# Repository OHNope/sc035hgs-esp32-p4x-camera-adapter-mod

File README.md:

# SC035HGS Camera Adapter Mod

[中文](#中文) | [English](#english)

---

## 中文

本仓库在 [ESP32-P4X_MIPI_Camera_Sub_V1.1_KiCAD](https://github.com/OHNope/ESP32-P4X_MIPI_Camera_Sub_V1.1_KiCAD)（Espressif 官方相机转接板的 KiCad 转换版）基础上，修改为 SC035HGS 相机模组用的转接板。基础工程（导入修复、检查结果）的说明见它的 [README](https://github.com/OHNope/ESP32-P4X_MIPI_Camera_Sub_V1.1_KiCAD#readme)。

### 原理图改动

依据：SC035HGS 数据手册 V0.8、模组图纸（24P FPC，0.5 mm 间距，0.3 mm 厚，触点在模组背面）、[ESP32-P4-Function-EV-Board v1.5.2 原理图](sources/esp32-p4-function-ev-board-schematics_v1.52.pdf)。模组图纸上标的传感器是 SC035GS；SC035HGS 是它的升级版，完全兼容，FPC 引脚定义不变。

**J2（模组 FPC）**：沿用原连接器 FPC-05F-24PH20（24P，0.5 mm，翻盖下接）和封装 `Camera_Sub:FFC_24P_0P5`。FPC 触点朝下插入时，模组第 n 脚落在焊盘 n 上，所以封装几何不变，只重做引脚定义。新符号 `SC035HGS_Mod:SC035HGS_FPC_24P` 的引脚名与模组图纸一致：

| J2 | 模组 | 网络 | J2 | 模组 | 网络 |
|----|------|------|----|------|------|
| 1 | LED-strobe | `/LED_STROBE` | 13–16 | NC | — |
| 2 | TRIG | `/TRIG` | 17, 20 | GND | GND |
| 3 | PWDN (xshutdn) | `/XSHUTDN` | 18 / 19 | MIPI_RCN / RCP | `/CSI_CLKN` / `/CSI_CLKP` |
| 4 | NC | — | 21 | MCLK | `/MCLK` |
| 5 / 6 | SDA / SCL | `/SENSOR_SDA` / `/SENSOR_SCL` | 22 | DOVDD 1.8 V | DOVDD_1V8 |
| 7, 8 | GND | GND | 23 | DVDD 1.5 V | DVDD_1V5 |
| 9 / 10 | MIPI_RDN0 / RDP0 | `/CSI_DATA0N` / `P` | 24 | AVDD 2.8 V | AVDD_2V8 |
| 11 / 12 | MIPI_RDN1 / RDP1 | `/CSI_DATA1N` / `P` | 25, 26 | 固定焊盘 | GND |

**电源**：新增 U3 ME6211C15M5G-N（LCSC C53100）提供 DVDD 1.5 V。上电顺序按手册 DOVDD → DVDD → AVDD：U1 EN 接 3V3，U3 EN 经 R12/C18 接 DOVDD_1V8，U2 EN 经 R14/C15 接 DVDD_1V5，各有约 1 ms 的 RC 延时，前一路稳定后下一路才开启。

**控制信号**：传感器侧都是 1.8 V（输入上限 DOVDD+0.3 V），主板和 J3 都是 3.3 V。三路都用 SN74LVC1G07 开漏缓冲（VCC=1.8 V，输入/输出可耐 5.5 V）做电平转换：

- XSHUTDN（U4）：输入 `/XSHUTDN_3V3` 来自 J1.5 和 J3.3，R24 上拉，默认使能。输出经 R10/C3 延时，XSHUTDN 在 DOVDD 上电或 J3.3 释放后约 12–14 ms 才达到高电平（手册只要求 AVDD 稳定后再拉高，T3 ≥ 0）。SW1 和 J3.3 拉低 XSHUTDN 是让传感器进入休眠，寄存器内容保留，并不是复位（手册 p.14）。原来 J1.5 直接接到 1.8 V 复位网络，主板 3.3 V 上拉和板上 1.8 V 上拉分压后约 2.55 V，超过 SC035HGS 的绝对最大值，所以改为缓冲。
- TRIG（U5）：J3.1 → TRIG，R26 2.2 kΩ 上拉，R25 让 J3 悬空时保持低电平。外触发模式下上升沿开始曝光。
- LED_STROBE（U6）：J2.1 → J3.2，R28 上拉到 3V3，R27 让传感器关断时输出保持低电平。

**J3**：JAE IL-G-4P-S3L2-SA（2.5 mm 间距，卧式，摩擦锁），线端配 IL-G-4S-S3C2-SA。1 TRIG_3V3、2 LED_STROBE_3V3、3 XSHUTDN_3V3、4 GND，接到 P4 开发板的 GPIO 排针。封装 `SC035HGS_Mod:JAE_IL-G-4P-S3L2-SA_1x04_P2.50mm_Horizontal` 按 JAE 图纸 SJ019575 画：1 脚编号与 JAE 一致（元件面看，开口朝 +Y 时 1 脚在左），孔径 1.1 mm，焊盘沿用社团的椭圆焊盘；板边应距针排 7–8.5 mm。注意：社团原有 IL-G 封装的 1 脚编号与 JAE 相反，用社团线束时要按 JAE 编号核对。EV 板 CSI 座的 CAM_IO0/CAM_IO1（对应 J1.5/J1.4）没有接到任何 GPIO，CAM_IO0 只有上拉（EV-Board 原理图 p.3：J9.11 CAM_IO0 只接 R123 10 kΩ 到 3.3 V，J9.12 CAM_IO1 的 R111 不贴），所以必须通过 J3 控制。J1.4 保持不接。

**C12/C13/C14**：值标为 NC 的三颗电容在原理图和 PCB 上都设为 DNP（不贴）。

**网络改名**：`RESET` → `XSHUTDN`（1.8 V）/ `XSHUTDN_3V3`（3.3 V），`XVCLK` → `MCLK`。新增器件放在项目库 `libraries/SC035HGS_Mod.*`（符号和封装），连接器出线方向等元数据在 `libraries/manifest.json`；`orcad_import` / `Camera_Sub` 与上游保持一致。

**固件注意**：
- 首次 I2C 访问：XSHUTDN 变高且 MCLK 已在运行后至少等 4 ms（手册 p.13 图 1-4 的 T4）。板上 XSHUTDN 由 R10/C3 延时，所以上电或释放 J3.3 后至少等约 20 ms 再访问传感器。
- 需要恢复默认寄存器时写 `0x0103=0x01`（软复位），拉低 XSHUTDN 不会清除寄存器。
- MCLK 为 24 MHz。写 `0x0100=0x01` 后至少等 7 ms，再写 `0x4418`/`0x4419`（SmartSens 配置说明）。
- 外触发模式：`0x3222[1]=1`。STROBE 使能：`0x3361[7:6]=00`。
- I2C 地址由模组内部的 SID0/SID1 决定（FPC 未引出），首次上电请扫描 0x30–0x33 确认。

### PCB

PCB 在 KiCad 里按新原理图更新后全部重做：旧铜皮全部删除，重新摆放和走线。

- **板框与叠层**：40 × 24 mm，R3 圆角。4 层，嘉立创 JLC04161H-7628 叠层，1.6 mm，沉金（ENIG）；加工参数在 [`pcb-fabrication-profile.json`](pcb-fabrication-profile.json)，Board Setup 的工艺下限也按它设置。
- **布局**：J1（接 P4 开发板的 FPC）在下边，J2（模组 FPC）在上边，J3 在右边、开口朝板外，SW1 在右上角。
- **层分配**：In1 整层 GND，In2 整层 DOVDD_1V8；顶层和底层走信号并铺 GND。3V3、DVDD_1V5、AVDD_2V8 走线，线宽按 SC035HGS 最大 120 mW 的电流算，对应网络类 `PWR_*`。
- **MIPI CSI-2**：三对差分全部走顶层、不打孔，100 Ω（线宽 0.2258 mm，间距 0.2032 mm），以 In1 为参考面；每次转弯只用一个 45° 折角，对内长度差为 0，三对之间的长度差 0.21 mm。
- **过孔**：全部 0.6/0.3 mm。
- **丝印**：字高 1.0 mm、线宽 0.15 mm（嘉立创下限）；放不下的位号移到 Fab 层。底面丝印为板名和 "Same-Side FFC" 提示。
- **清理**：删除了 Allegro 导入时留下的尺寸标注（MECH1/MECH2）、钻孔表、板外的空规则区和右边缘的旧 Route Keepin 规则区；底面丝印上 Espressif 的 logo 和 WEEE/ESD/无铅/无卤标志也已删除。
- **位置**：板子放在 A4 图框正中（板框 x 128.5–168.5 mm，y 93–117 mm），出图时板子在图框内。
- **检查**：ERC 0；DRC 0 错误、0 未连接，与原理图一致。剩余 87 条警告都是丝印：57 条是相邻 `Camera_Sub` 库封装的丝印互相碰到（封装丝印超出 courtyard），30 条是丝印压在焊盘上（主要是 J1/SW1，生产时由阻焊裁掉），不影响加工。

`sources/espressif-original/` 里是 Espressif 原板的 BOM、贴片坐标和 PCB 加工说明，对应的是旧版 32 mm 板，**不能用来给本板下单**。本板的 Gerber、BOM 和贴片文件由 `-fab` 发布生成，下单用最新的 `v0.9.1-fab`。

### 上电调试

首批板子上电时逐项确认，结果补记在这里：

- [ ] **MCLK 占空比**：Y1 没有可查的数据手册。在 J2.21 测 24 MHz 波形，占空比应在 45–55 %，高、低电平各至少 5 ns（SC035HGS 手册 p.37）。
- [ ] **各路电流**：手册 V0.8 p.36 的工作电流是空白的，分别测 DOVDD_1V8、DVDD_1V5、AVDD_2V8 的电流。按手册 p.2 的最大功耗 120 mW 推算，单路上限约为 DOVDD 67 mA、DVDD 80 mA、AVDD 43 mA，都在 ME6211 的额定范围内；测得值明显更大时先断电排查。
- [ ] **I2C 地址**：在 0x30–0x33 范围扫描，记下模组的实际地址。
- [ ] **J3 → P4 GPIO**：J3 接 EV 板的 GPIO 排针（J1，2×20）时，避开启动 strapping 引脚 GPIO34–GPIO38；排针上是 GPIO37（8 脚）、GPIO38（10 脚）和 GPIO36（24 脚）（EV-Board 原理图 p.3）。P4 复位期间本板会给 J3 加上固定电平：J3.3 经 R24 上拉到 3V3，J3.1 经 R25 下拉，DOVDD 有电且 STROBE 空闲时 J3.2 被 U6 拉低，接在 strapping 引脚上可能改变启动模式。J3.1（TRIG）和 J3.3（XSHUTDN）的 GPIO 设为推挽输出（U4/U5 的输入要求快边沿），J3.2（STROBE）设为输入，J3.4 接排针上的 GND。选定的 GPIO 记在这里。
- [ ] **J3 实物配合（可选）**：封装已按 JAE 图纸 SJ019575 核对；有 IL-G-4P-S3L2-SA 样品时，可再实际插装确认孔位和板边距离。

**已接受的风险**（2026-10-03 决定本版不改）：

- **突然断电时的 XSHUTDN**：手册图 1-5 要求断电前先拉低 XSHUTDN。3V3 突然断开时，C3（R10 × C3 = 10 ms）会让 XSHUTDN 在 DOVDD 已经下降后仍短暂保持高电平，可能超过 DOVDD + 0.3 V 的绝对最大值。能量很小，Espressif 原板的 RESET RC 也是如此。正常关机时先把 J3.3 拉低再断电即可避免。若要修改：在 R10 两端并联一个二极管（阳极接 /XSHUTDN，阴极接 DOVDD_1V8）。
- **U4 直接给 C3 放电**：U4 拉低 XSHUTDN 时，C3（1 µF）经 U4 输出直接放电，中间没有电阻。峰值灌电流只受 U4 输出电阻限制，超过推荐的 4 mA IOL，在几十微秒内可能接近 50 mA 的绝对最大值。若要修改：在 U4.4 与 R10/C3/J2.3 节点之间串 100–220 Ω。

**下一版待改**：U4 的 Description 字段写的是 "R10 + C3 set the >=4 ms power-up delay"，这个说法不对。手册的 4 ms（T4，p.13）是 XSHUTDN 变高到第一次 I2C 访问之间的时间，由固件等待（见上文“固件注意”）；R10/C3 的作用是让 XSHUTDN 在 AVDD 之后变高（T3 ≥ 0）。下一版改为 "R10 + C3 delay XSHUTDN high ~12 ms after DOVDD (T3 >= 0); firmware waits >= 4 ms (T4) before I2C"。这只是字段文字，不影响网表和 PCB，本版不改。

### 仓库关系

| Remote     | 仓库                                         | 用途                        |
|------------|----------------------------------------------|-----------------------------|
| `origin`   | `OHNope/sc035hgs-esp32-p4x-camera-adapter-mod` | 本仓库，改版开发            |
| `upstream` | `OHNope/ESP32-P4X_MIPI_Camera_Sub_V1.1_KiCAD`  | 基础工程，只拉取，不推送    |

基础工程有更新时合并进来：

```bash
git fetch upstream
git merge upstream/main
```

工程文件名 `SCH_ESP32-P4_FUNCTION_EV_BOARD_MIPI_Camera_Sub_V1.1_20240529.*` 与基础工程保持一致，不要改名，否则上游修改无法直接合并。本仓库的 README.md 是改版说明，合并时 README.md 有冲突就保留本仓库的版本（`git checkout --ours README.md`）。

### 发布

[`.github/workflows/pcb-release.yml`](.github/workflows/pcb-release.yml) 调用共享流水线 [OHNope/kicad-release](https://github.com/OHNope/kicad-release)，标签规则、各次发布的内容和 Google Drive 配置都以那边的 README 为准。

| 标签 | 内容 |
|------|------|
| `v0.9.0` | 只有 SC035HGS 原理图，PCB 还是旧板 |
| `v0.9.1-fab` | 第一版 PCB 的加工文件（Gerber、钻孔、BOM、贴片坐标），用于打样；贴片坐标不含不贴的 C12–C14。没有单独的 `v0.9.1` 设计发布 |

```bash
git tag -a v0.9.1 -m "v0.9.1: ..." && git push origin v0.9.1
```

```bash
git tag -a v0.9.1-fab -m "v0.9.1-fab: ..." "v0.9.1^{}" && git push origin v0.9.1-fab
```

`v0.9.1` 发布原理图/PCB 文档，并把已提交的整个工程目录传到 Drive；`v0.9.1-fab` 才发布 Gerber，且必须与 `v0.9.1` 指向同一个 commit，所以先推设计标签、再推 `-fab`。C12–C14 在 F.Paste 上仍有钢网开口，下单 SMT 时以 BOM 和贴片坐标为准。Google Drive 需要在 Settings → Secrets and variables → Actions 中设置 secret `GDRIVE_TOKEN` 和 variable `GDRIVE_FOLDER_ID`。

### kicad-auto

`.kicad-auto/` 是 kicad-auto 工具的本地状态（评审、语义分析、生成工作区），已加入 `.gitignore`，不提交。

### 版权与许可

设计版权归 Espressif Systems (Shanghai) Co., Ltd. 所有。本仓库**不授予任何许可**，详见 [LICENSE](LICENSE)。本仓库为非营利性的学习与参考分享，与 Espressif 无关联、未获其背书；如 Espressif 提出异议，将立即删除。

---

## English

This repository modifies [ESP32-P4X_MIPI_Camera_Sub_V1.1_KiCAD](https://github.com/OHNope/ESP32-P4X_MIPI_Camera_Sub_V1.1_KiCAD), the KiCad conversion of Espressif's camera adapter board, into an adapter for the SC035HGS camera module. See its [README](https://github.com/OHNope/ESP32-P4X_MIPI_Camera_Sub_V1.1_KiCAD#readme) for the base project (import fixes, check results).

### Schematic changes

Sources: SC035HGS datasheet V0.8, the module drawing (24-pin FPC, 0.5 mm pitch, 0.3 mm thick, contacts on the module's bottom side), [ESP32-P4-Function-EV-Board v1.5.2 schematic](sources/esp32-p4-function-ev-board-schematics_v1.52.pdf). The module drawing names the sensor SC035GS; SC035HGS is its fully compatible upgrade, so the FPC pinout is unchanged.

- **J2 (module FPC)**: same connector (FPC-05F-24PH20, 24-pin 0.5 mm flip-lock, bottom contact) and footprint `Camera_Sub:FFC_24P_0P5`. With the FPC inserted contacts-down, module pin n lands on pad n, so only the pin assignment changes. The new symbol `SC035HGS_Mod:SC035HGS_FPC_24P` uses the module's pin names; see the table in the Chinese section.
- **Power**: U3 ME6211C15M5G-N (LCSC C53100) adds DVDD 1.5 V. Power-up order follows the datasheet (DOVDD → DVDD → AVDD): U1 EN from 3V3, U3 EN from DOVDD_1V8 through R12/C18, U2 EN from DVDD_1V5 through R14/C15. Each RC adds about 1 ms, so a rail starts only after the previous one has settled.
- **Control signals**: the sensor side is 1.8 V (inputs limited to DOVDD + 0.3 V), and the main board and J3 are 3.3 V. Three SN74LVC1G07 open-drain buffers at VCC = 1.8 V (5.5 V-tolerant input and output) translate them:
  - XSHUTDN (U4): input `/XSHUTDN_3V3` from J1.5 and J3.3, pulled up by R24 (enabled by default). R10/C3 on the output delay it: XSHUTDN reaches a valid high about 12–14 ms after DOVDD comes up or J3.3 is released (the datasheet only requires it after AVDD is stable, T3 ≥ 0). Pulling XSHUTDN low with SW1 or J3.3 puts the sensor to sleep with its registers kept; it is not a reset (datasheet p.14). J1.5 used to sit directly on the 1.8 V reset net, where the main board's 3.3 V pull-up and the local 1.8 V pull-up divided to about 2.55 V, above the sensor's absolute maximum.
  - TRIG (U5): J3.1 → TRIG, 2.2 kΩ pull-up (R26). R25 holds it low when J3 is open. In external-trigger mode a rising edge starts exposure.
  - LED_STROBE (U6): J2.1 → J3.2, pulled up to 3V3 by R28. R27 holds it low while the sensor is off.
- **J3**: JAE IL-G-4P-S3L2-SA (2.5 mm pitch, right-angle, friction lock); mating socket IL-G-4S-S3C2-SA. 1 TRIG_3V3, 2 LED_STROBE_3V3, 3 XSHUTDN_3V3, 4 GND, wired to the P4 board's GPIO header. The footprint `SC035HGS_Mod:JAE_IL-G-4P-S3L2-SA_1x04_P2.50mm_Horizontal` follows JAE drawing SJ019575: JAE terminal numbering (pin 1 on the left seen from the component side with the opening toward +Y), 1.1 mm holes, the club's oval pads; keep the board edge 7–8.5 mm from the pin row. Note that the club's original IL-G footprints number the pins in the opposite direction, so check club harnesses against the JAE numbering. CAM_IO0/CAM_IO1 on the EV board's CSI connector (J1.5/J1.4 here) reach no GPIO, and CAM_IO0 has only a pull-up (EV-Board schematic p.3: J9.11 CAM_IO0 has only R123 10 kΩ to 3.3 V; R111 on J9.12 CAM_IO1 is not fitted), so XSHUTDN has to be controlled through J3. J1.4 stays unconnected.
- **C12/C13/C14**: the three capacitors valued NC are DNP (not fitted) in both schematic and PCB.
- **Net renames**: `RESET` → `XSHUTDN` (1.8 V) / `XSHUTDN_3V3` (3.3 V), `XVCLK` → `MCLK`. New parts live in the project library `libraries/SC035HGS_Mod.*` (symbols and footprints), with connector metadata such as cable direction in `libraries/manifest.json`. `orcad_import` and `Camera_Sub` stay identical to upstream.
- **Firmware notes**:
  - First I2C access: wait at least 4 ms after XSHUTDN goes high with MCLK running (datasheet p.13, Fig. 1-4, T4). XSHUTDN is delayed by R10/C3, so wait about 20 ms after power-up or after releasing J3.3.
  - To restore default registers, write `0x0103=0x01` (soft reset); pulling XSHUTDN low does not clear them.
  - MCLK is 24 MHz. Wait at least 7 ms after writing `0x0100=0x01` before writing `0x4418`/`0x4419` (SmartSens configuration note).
  - External trigger mode: `0x3222[1]=1`. Strobe enable: `0x3361[7:6]=00`.
  - The I2C address depends on SID0/SID1 inside the module (not on the FPC). Scan 0x30–0x33 on first power-up.

### PCB

The PCB was updated from the new schematic in KiCad and then redone: all old copper was removed, the parts re-placed and the board re-routed.

- **Outline and stackup**: 40 × 24 mm with R3 corners. 4 layers on JLCPCB's JLC04161H-7628 stackup, 1.6 mm, ENIG. The fabrication parameters are in [`pcb-fabrication-profile.json`](pcb-fabrication-profile.json), which also sets the Board Setup manufacturing minimums.
- **Placement**: J1 (FPC to the P4 board) on the bottom edge, J2 (module FPC) on the top edge, J3 on the right edge opening outward, SW1 in the top-right corner.
- **Layers**: In1 is a solid GND plane and In2 a solid DOVDD_1V8 plane; top and bottom carry signals and GND pours. 3V3, DVDD_1V5 and AVDD_2V8 are tracks sized for the SC035HGS's 120 mW maximum, in the `PWR_*` netclasses.
- **MIPI CSI-2**: all three pairs on the top layer with no vias, 100 Ω (0.2258 mm width, 0.2032 mm gap) over the In1 reference; a single 45° bend at each turn, zero skew within each pair and 0.21 mm length difference between pairs.
- **Vias**: all 0.6/0.3 mm.
- **Silkscreen**: 1.0 mm text height and 0.15 mm stroke (JLCPCB's minimum); references that do not fit are on the Fab layer. The bottom silkscreen carries the board name and a "Same-Side FFC" note.
- **Cleanup**: the Allegro import's dimension annotations (MECH1/MECH2), drill chart, off-board empty rule areas and the stale Route Keepin area on the right edge are removed, as are Espressif's logo and the WEEE/ESD/Pb-free/halogen-free marks on the bottom silkscreen.
- **Position**: the board sits in the middle of the A4 drawing sheet (outline x 128.5–168.5 mm, y 93–117 mm), so plots show it inside the frame.
- **Checks**: ERC 0; DRC 0 errors and 0 unconnected, schematic and PCB in sync. The 87 remaining warnings are all silkscreen: 57 where neighbouring `Camera_Sub` library footprints' silkscreen touches (it extends past their courtyards) and 30 where silkscreen crosses pads (mostly J1/SW1, clipped by the solder mask at fabrication). None affects fabrication.

`sources/espressif-original/` holds Espressif's BOM, placement file and PCB fabrication notes for the original 32 mm board. **Do not order this board from them.** This board's Gerbers, BOM and placement file come from the `-fab` releases; order from the latest, `v0.9.1-fab`.

### Bring-up

Check these on the first powered boards and record the results here:

- [ ] **MCLK duty cycle**: Y1 has no datasheet on file. Measure the 24 MHz waveform at J2.21: duty cycle 45–55 %, high and low time at least 5 ns each (SC035HGS datasheet p.37).
- [ ] **Rail currents**: datasheet V0.8 leaves the operating currents on p.36 blank. Measure DOVDD_1V8, DVDD_1V5 and AVDD_2V8 separately. The 120 mW maximum on p.2 bounds a single rail to about 67 mA DOVDD, 80 mA DVDD or 43 mA AVDD, all within the ME6211 ratings; power down and investigate if a reading is clearly higher.
- [ ] **I2C address**: scan 0x30–0x33 and note the module's actual address.
- [ ] **J3 → P4 GPIOs**: when wiring J3 to the EV board's GPIO header (J1, 2×20), avoid the boot-strapping pins GPIO34–GPIO38; on the header these are GPIO37 (pin 8), GPIO38 (pin 10) and GPIO36 (pin 24) (EV-Board schematic p.3). This board holds J3 at fixed levels while the P4 is in reset (J3.3 pulled up to 3V3 by R24, J3.1 pulled down by R25, J3.2 sunk by U6 whenever DOVDD is up and STROBE idles), which could change the boot mode on a strapping pin. Drive the J3.1 (TRIG) and J3.3 (XSHUTDN) GPIOs push-pull, since the U4/U5 inputs need fast edges; configure J3.2 (STROBE) as an input and tie J3.4 to a header GND. Record the chosen GPIOs here.
- [ ] **J3 fit (optional)**: the footprint is checked against JAE drawing SJ019575. If an IL-G-4P-S3L2-SA sample is available, also confirm the hole positions and edge distance with the real part.

**Accepted risks** (decided 2026-10-03; not changed in this revision):

- **XSHUTDN on sudden power loss**: the datasheet (Fig. 1-5) wants XSHUTDN low before the supplies go off. If 3V3 drops out suddenly, C3 (R10 × C3 = 10 ms) keeps XSHUTDN high briefly after DOVDD has fallen, possibly above the DOVDD + 0.3 V absolute maximum. The energy is small and Espressif's RESET RC behaves the same way. Pulling J3.3 low before removing power avoids it in a normal shutdown. To change it: a diode across R10 (anode on /XSHUTDN, cathode on DOVDD_1V8).
- **U4 discharges C3 directly**: when U4 pulls XSHUTDN low it discharges C3 (1 µF) with no series resistor. The peak sink current is limited only by U4's output resistance; it exceeds the recommended 4 mA IOL and may approach the 50 mA absolute maximum for tens of microseconds. To change it: 100–220 Ω between U4.4 and the R10/C3/J2.3 node.

**Next revision**: U4's Description field says "R10 + C3 set the >=4 ms power-up delay", which is wrong. The datasheet's 4 ms (T4, p.13) runs from XSHUTDN high to the first I2C access and is a firmware wait (see the firmware notes above); R10/C3 make XSHUTDN rise after AVDD (T3 ≥ 0). Change it to "R10 + C3 delay XSHUTDN high ~12 ms after DOVDD (T3 >= 0); firmware waits >= 4 ms (T4) before I2C". The field is text only and affects neither the netlist nor the PCB, so this revision keeps it.

### Remotes

| Remote     | Repository                                     | Role                          |
|------------|------------------------------------------------|-------------------------------|
| `origin`   | `OHNope/sc035hgs-esp32-p4x-camera-adapter-mod` | This repository, mod work     |
| `upstream` | `OHNope/ESP32-P4X_MIPI_Camera_Sub_V1.1_KiCAD`  | Base project, fetch only      |

Merge base-project updates with:

```bash
git fetch upstream
git merge upstream/main
```

Keep the project file names `SCH_ESP32-P4_FUNCTION_EV_BOARD_MIPI_Camera_Sub_V1.1_20240529.*` identical to the base project. Renaming them stops upstream changes from merging cleanly. This repository's README.md describes the mod; if a merge conflicts on it, keep this repository's version (`git checkout --ours README.md`).

### Release

[`.github/workflows/pcb-release.yml`](.github/workflows/pcb-release.yml) calls the shared pipeline in [OHNope/kicad-release](https://github.com/OHNope/kicad-release), which documents the tags, what each release contains and the Google Drive setup.

| Tag | Contents |
|-----|----------|
| `v0.9.0` | SC035HGS schematic only; the PCB is still the old board |
| `v0.9.1-fab` | Fabrication files for the first PCB (Gerbers, drill, BOM, placement), for the prototype order; the placement file leaves out the DNP parts C12–C14. There is no separate `v0.9.1` design release |

```bash
git tag -a v0.9.1 -m "v0.9.1: ..." && git push origin v0.9.1
```

```bash
git tag -a v0.9.1-fab -m "v0.9.1-fab: ..." "v0.9.1^{}" && git push origin v0.9.1-fab
```

`v0.9.1` publishes the schematic/PCB documents and uploads the committed project tree to Drive. `v0.9.1-fab` publishes the Gerbers and must point at the same commit as `v0.9.1`, so push the design tag before the `-fab` tag. C12–C14 still have F.Paste apertures; for SMT assembly, the BOM and placement file decide what gets fitted. For Google Drive, set the secret `GDRIVE_TOKEN` and the variable `GDRIVE_FOLDER_ID` in Settings → Secrets and variables → Actions.

### kicad-auto

`.kicad-auto/` holds kicad-auto's machine-local state (reviews, semantic analysis, generation workspaces). It is in `.gitignore` and is never committed.

### Copyright and license

The design is copyright Espressif Systems (Shanghai) Co., Ltd. This repository **grants no license**; see [LICENSE](LICENSE). It is a non-commercial share for study and reference, is not affiliated with or endorsed by Espressif, and will be taken down if Espressif objects.

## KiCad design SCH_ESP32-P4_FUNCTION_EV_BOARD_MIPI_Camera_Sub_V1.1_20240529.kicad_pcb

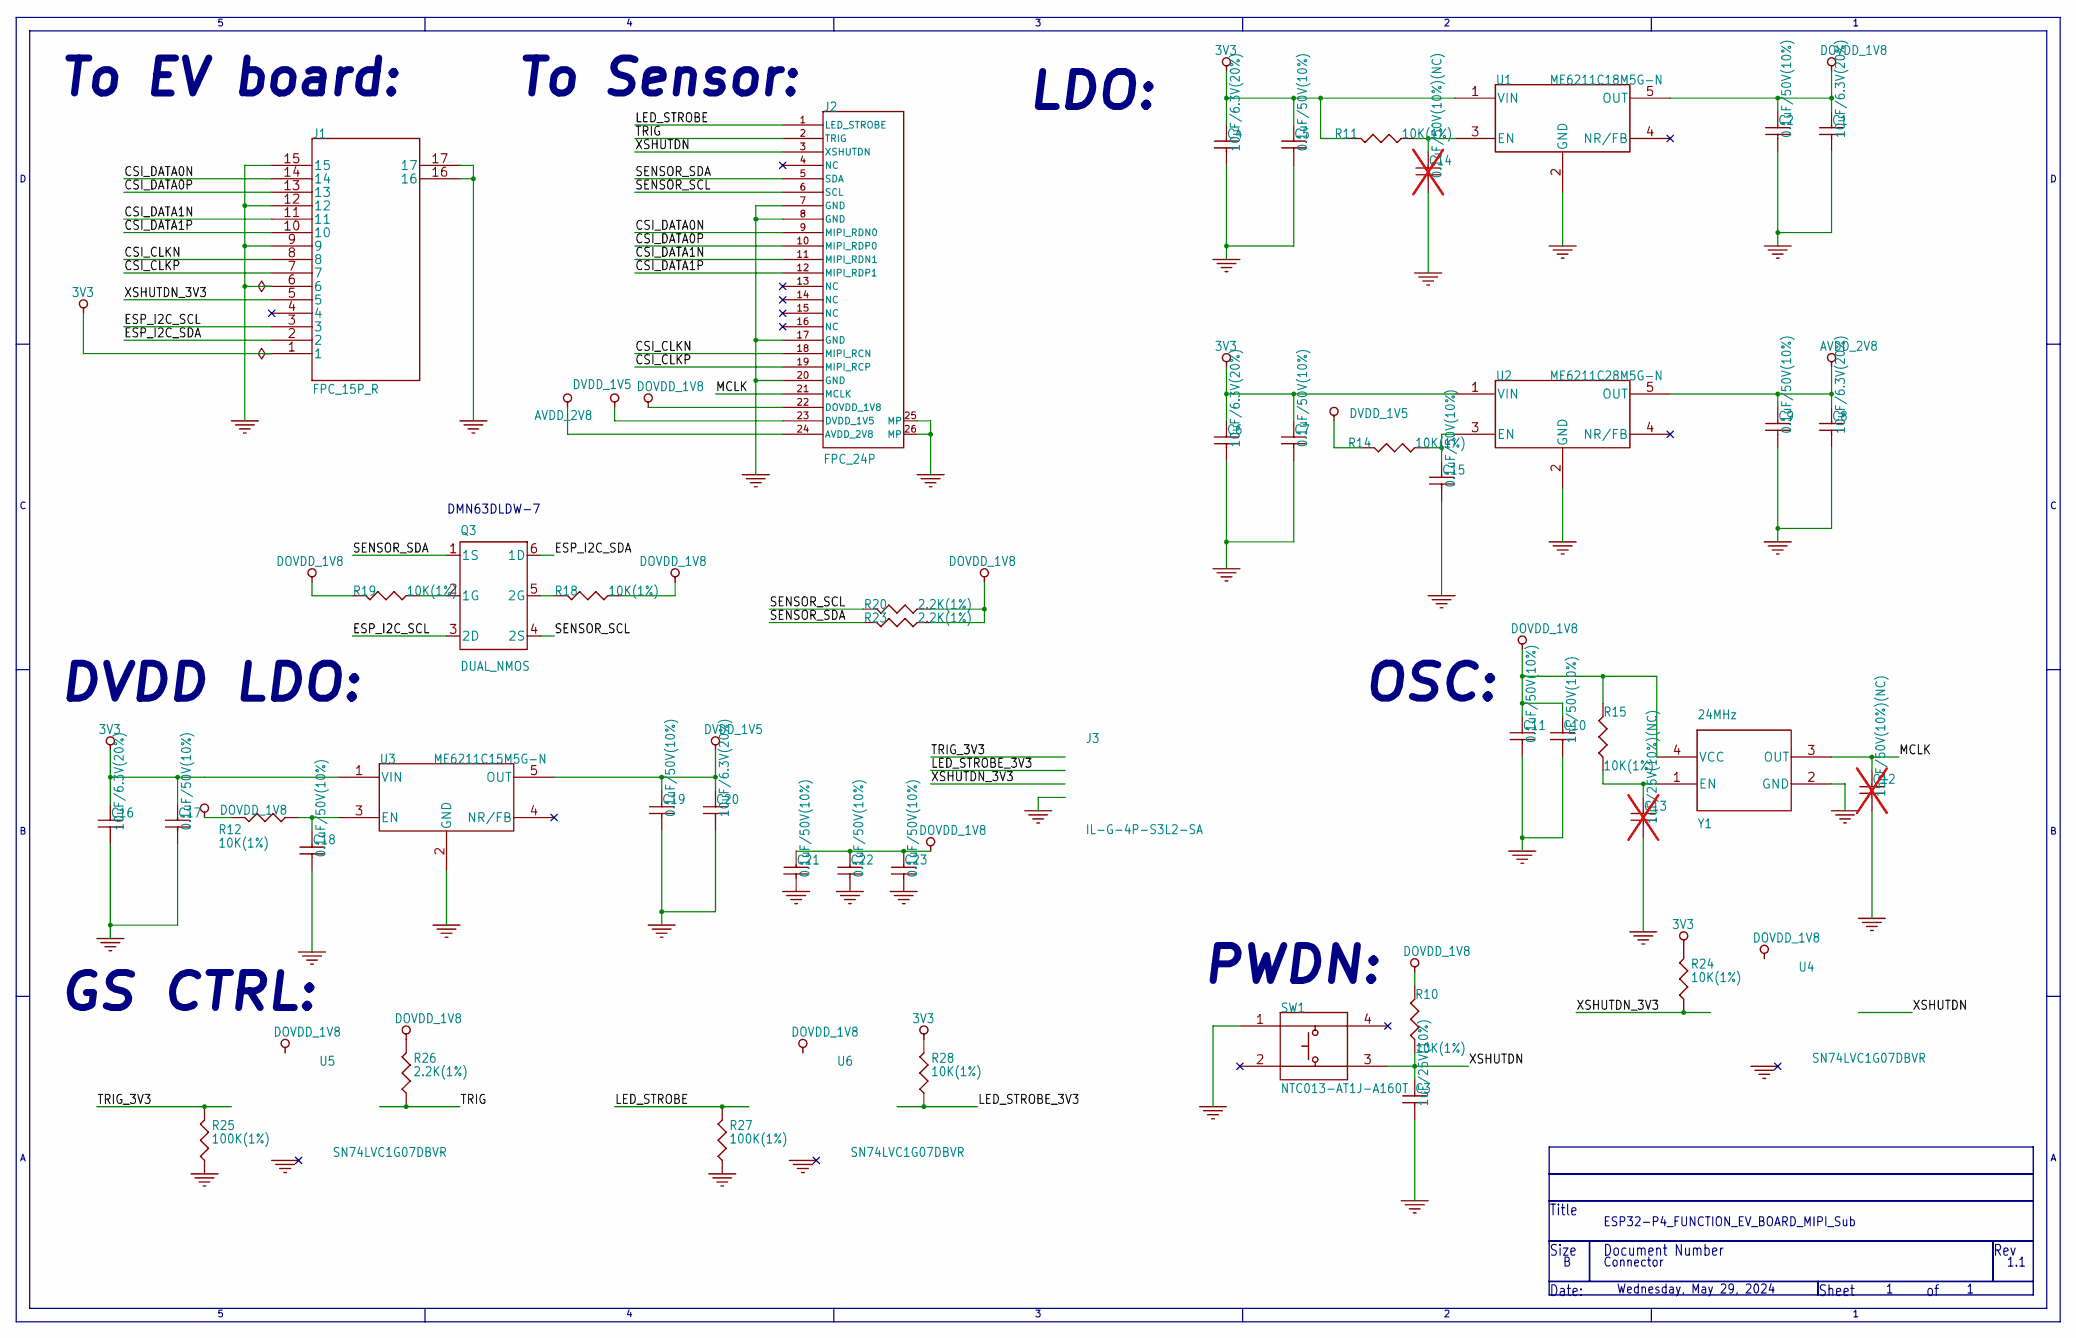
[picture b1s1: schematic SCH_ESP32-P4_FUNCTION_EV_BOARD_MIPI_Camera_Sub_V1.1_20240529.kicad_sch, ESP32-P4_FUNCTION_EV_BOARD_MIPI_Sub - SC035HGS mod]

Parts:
C1, C4, C6, C8, C16, C20: 10uF/6.3V(20%); C0603
C2, C5, C7, C9, C11, C15, C17, C18, C19, C21, C22, C23: 0.1uF/50V(10%); C0402; Part Number ES110451066200
C3: 1uF/25V(10%); C0402; Part Number ES110451066200
C10: 1nF/50V(10%); C0402; Part Number ES110451066200
C12: 15pF/50V(10%)(NC); C0402; Part Number ES110451066200; not fitted
C13: 1uF/25V(10%)(NC); C0402; Part Number ES110451066200; not fitted
C14: 0.1uF/50V(10%)(NC); C0402; Part Number ES110451066200; not fitted
J1: FPC_15P_R; FFC_15P_1_MIPI_R; MPN AFA07-S15FCA-00
J2: FPC_24P; FFC_24P_0P5; MPN FPC-05F-24PH20
J3: IL-G-4P-S3L2-SA; JAE_IL-G-4P-S3L2-SA_1x04_P2.50mm_Horizontal; MPN IL-G-4P-S3L2-SA
Q3: DUAL_NMOS; SOT-363; MPN DMN63D8LDW-7
R10, R11, R12, R14, R15, R18, R19, R24, R28: 10K(1%); R0402; Part Number ES210400000000
R20, R23, R26: 2.2K(1%); R0402; Part Number ES210400000000
R25, R27: 100K(1%); R0402; Part Number ES210400000000
SW1: NTC013-AT1J-A160T; SW4-4P2X3P2X2P5-SMT; Part Number ES511600400000
U1: ME6211C18M5G-N; SOT23-5; Part Number ES41140207000000
U2: ME6211C28M5G-N; SOT23-5; Part Number ES41140207000000
U3: ME6211C15M5G-N; SOT23-5; Part Type Power ICs
U4, U5, U6: SN74LVC1G07DBVR; SOT23-5; MPN SN74LVC1G07DBVR
Y1: 24MHz; XTAL3225; MPN 2.1.3.2400037

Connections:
3V3: C4.1, C5.1, C6.1, C7.1, C16.1, C17.1, J1.1, R11.2, R24.2, R28.2, U1.1 (VIN), U2.1 (VIN), U3.1 (VIN)
/CSI_CLKN: J1.8, J2.18 (MIPI_RCN)
/CSI_CLKP: J1.7, J2.19 (MIPI_RCP)
/CSI_DATA0N: J1.14, J2.9 (MIPI_RDN0)
/CSI_DATA0P: J1.13, J2.10 (MIPI_RDP0)
/CSI_DATA1N: J1.11, J2.11 (MIPI_RDN1)
/CSI_DATA1P: J1.10, J2.12 (MIPI_RDP1)
/ESP_I2C_SCL: J1.3, Q3.3 (2D)
/ESP_I2C_SDA: J1.2, Q3.6 (1D)
/LED_STROBE: J2.1 (LED_STROBE), R27.2, U6.2
/LED_STROBE_3V3: J3.2, R28.1, U6.4
/MCLK: C12.1, J2.21 (MCLK), Y1.3 (OUT)
/SENSOR_SCL: J2.6 (SCL), Q3.4 (2S), R20.2
/SENSOR_SDA: J2.5 (SDA), Q3.1 (1S), R23.2
/TRIG: J2.2 (TRIG), R26.1, U5.4
/TRIG_3V3: J3.1, R25.2, U5.2
/XSHUTDN: C3.1, J2.3 (XSHUTDN), R10.1, SW1.3, U4.4
/XSHUTDN_3V3: J1.5, J3.3, R24.1, U4.2
AVDD_2V8: C8.1, C9.1, J2.24 (AVDD_2V8), U2.5 (OUT)
DOVDD_1V8: C1.1, C2.1, C10.1, C11.1, C21.1, C22.1, C23.1, J2.22 (DOVDD_1V8), R10.2, R12.2, R15.2, R18.1, R19.2, R20.1, R23.1, R26.2, U1.5 (OUT), U4.5 (VCC), U5.5 (VCC), U6.5 (VCC), Y1.4 (VCC)
DVDD_1V5: C19.1, C20.1, J2.23 (DVDD_1V5), R14.2, U3.5 (OUT)
GND: C1.2, C2.2, C3.2, C4.2, C5.2, C6.2, C7.2, C8.2, C9.2, C10.2, C11.2, C12.2, C13.2, C14.2, C15.2, C16.2, C17.2, C18.2, C19.2, C20.2, C21.2, C22.2, C23.2, J1.6, J1.9, J1.12, J1.15, J1.16, J1.17, J2.7 (GND), J2.8 (GND), J2.17 (GND), J2.20 (GND), J2.25 (MP), J2.26 (MP), J3.4, R25.1, R27.1, SW1.1, U1.2 (GND), U2.2 (GND), U3.2 (GND), U4.3 (GND), U5.3 (GND), U6.3 (GND), Y1.2 (GND)
unnamed: Q3.2 (1G), R19.1
unnamed: Q3.5 (2G), R18.2
unnamed: C14.1, R11.1, U1.3 (EN)
unnamed: C15.1, R14.1, U2.3 (EN)
unnamed: C18.1, R12.1, U3.3 (EN)
unnamed: C13.1, R15.1, Y1.1 (EN)

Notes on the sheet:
OSC:
Size
DMN63DLDW-7
DVDD LDO:
Connector
1.1
PWDN:
Document Number
Wednesday, May 29, 2024
Rev
LDO:
Sheet
ESP32-P4_FUNCTION_EV_BOARD_MIPI_Sub
Title
To EV board:
GS CTRL:
Date:
To Sensor:

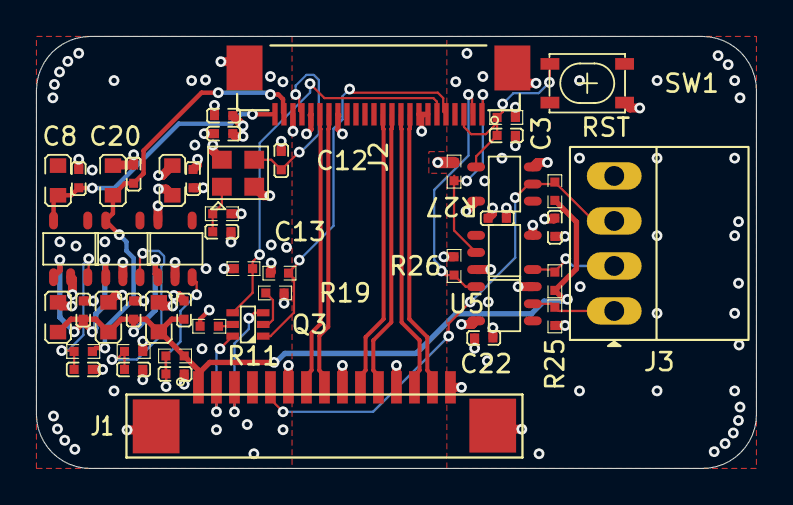
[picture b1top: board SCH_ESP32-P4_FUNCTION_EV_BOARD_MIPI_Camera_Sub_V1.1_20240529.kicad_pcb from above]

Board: 4 copper layers, 40.0 x 24.0 mm, 49 parts (0 on the bottom side), 28 nets.
